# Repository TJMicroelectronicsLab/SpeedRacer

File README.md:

# SpeedRacer
 ESP32 lidar w/ control

To set up arduino for the ESP32, follow these instructions

https://microcontrollerslab.com/install-esp32-arduino-ide/

or any other similar resource. This will allow you to select the correct board, which is

"DOIT ESP32 DEVKIT V1"

In addition, the ServoESP32 library should also be installed via the library manager.

The code should compile after this.

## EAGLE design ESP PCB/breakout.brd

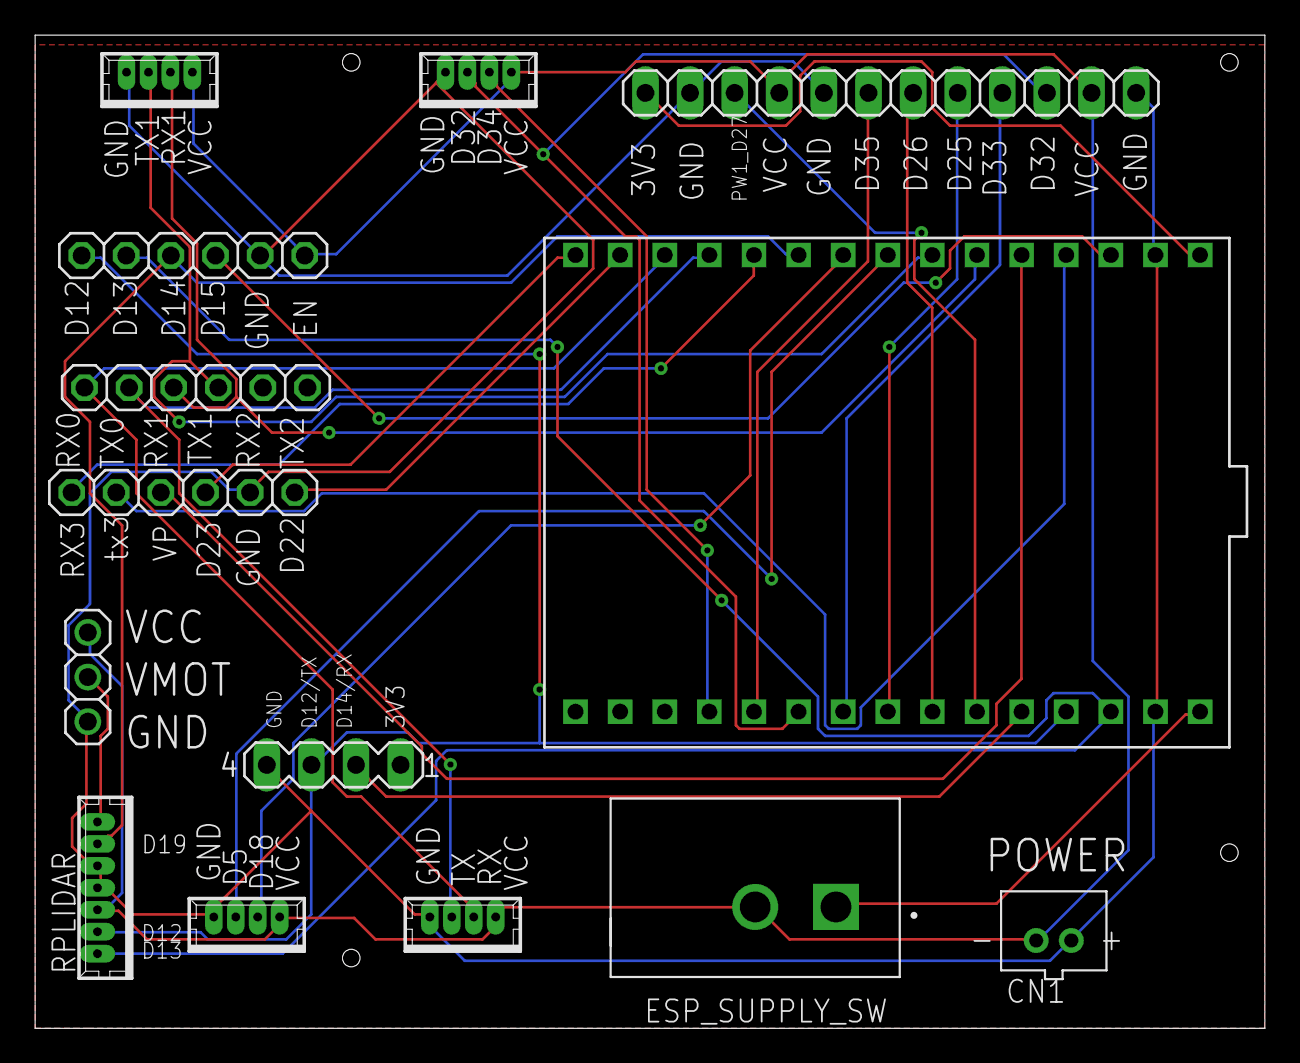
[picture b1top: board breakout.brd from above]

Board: 2 copper layers, 70.0 x 56.5 mm, 14 parts (0 on the bottom side), 28 nets.

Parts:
CN1: JST-PH-2-THM
ESP_SUPPLY_SW: GF-123-0054; SW_GF-123-0054
JP2: 1X12
JP3, JP4, JP5: 1X06
MOTOR_VOLTAGE: 1X03
RPLIDAR: 53047-07
SV1: MA04-1
U$1: ESP-32_30P_BKOUT; ESP32-30P
X1, X2, X3, X4: 53047-04

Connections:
D2: JP4.2, U$1.P$4
D4: JP4.3, U$1.P$5
D5: U$1.P$8, X4.3
D12: JP5.1, RPLIDAR.6, SV1.3, U$1.P$19
D13: JP5.2, RPLIDAR.7, U$1.P$18
D14: SV1.2, U$1.P$20
D15: JP5.4, U$1.P$3
D18: U$1.P$9, X4.2
D19: JP5.3, RPLIDAR.2, U$1.P$10
D21: JP4.1, U$1.P$11
D22: JP4.6, U$1.P$14
D23: JP4.4, U$1.P$15
D27: JP2.10, U$1.P$21
D32: JP2.3, U$1.P$25, X3.3
D34: U$1.P$27, X3.2
GND: CN1.1, JP2.1, JP2.8, JP2.11, JP4.5, JP5.5, MOTOR_VOLTAGE.1, RPLIDAR.3, RPLIDAR.4, SV1.4, U$1.P$2, U$1.P$17, X1.4, X2.4, X3.4, X4.4
unnamed: JP2.12, U$1.P$1
unnamed: JP2.4, U$1.P$24
unnamed: JP2.5, U$1.P$23
unnamed: JP2.6, U$1.P$22
unnamed: JP2.7, U$1.P$26
RX0: JP3.1, U$1.P$13, X1.2
RX1: JP3.3, U$1.P$6, X2.2
TX0: JP3.2, U$1.P$12, X1.3
TX1: JP3.4, U$1.P$7, X2.3
VCC: CN1.2, ESP_SUPPLY_SW.2, JP2.2, JP2.9, JP5.6, MOTOR_VOLTAGE.3, RPLIDAR.5, X1.1, X2.1, X3.1, X4.1
VESP: ESP_SUPPLY_SW.1, U$1.P$16
VMOT: MOTOR_VOLTAGE.2, RPLIDAR.1

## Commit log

2022-04-13 ESP PCB with spots for four TFMini connectors
    ESP points towards connectors. Next version reverses this.
2022-04-13 Add ESP32 Instructions
2022-04-14 STEP file of basic car platform
2022-04-14 fix data point array
    make sure data values are updated or zero on every loop
2022-04-14 Updated servo library to correct name
2022-04-14 scanCount slow, still WIP
2022-04-14 Revert "scanCount slow, still WIP"
    This reverts commit 387eb06c81d6a67858466fba074a9263565e3f82.
2022-04-14 speed up read loop
    stop bit not being found, only reading every delay seconds
2022-04-17 protocol rewrite
    Support Ultradense HQ mode
    Port from Slamtech API
2022-04-17 step on pull
2022-04-17 increase buffer size for scan
    completes full 360 scan, 4m range, 8k pts
2022-04-17 clean up
    quality is broken, not sure why, don't use until fixed
2022-04-17 clean up
2022-04-17 clean up speed racer
    add arguments back to init for rx tx
2022-04-17 make desc more sensible
2022-04-24 comments for calcs
2022-04-24 more clean up
    add comment that full 360 is available
2022-04-24 missed one
2022-04-24 Basic racer demo
2022-05-13 add lidar update count
    lidar.total_scan_count is incremented on every lidar update
2022-06-06 update pcb remove cam
2022-06-16 variable distance angle
    finds longest distance angle that is sufficiently large to contain car. Heads for center. Looks for close objects and tries to compensate steering angle. Checks center distance to implement variable 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
2023-02-28 added lidar datasheet
